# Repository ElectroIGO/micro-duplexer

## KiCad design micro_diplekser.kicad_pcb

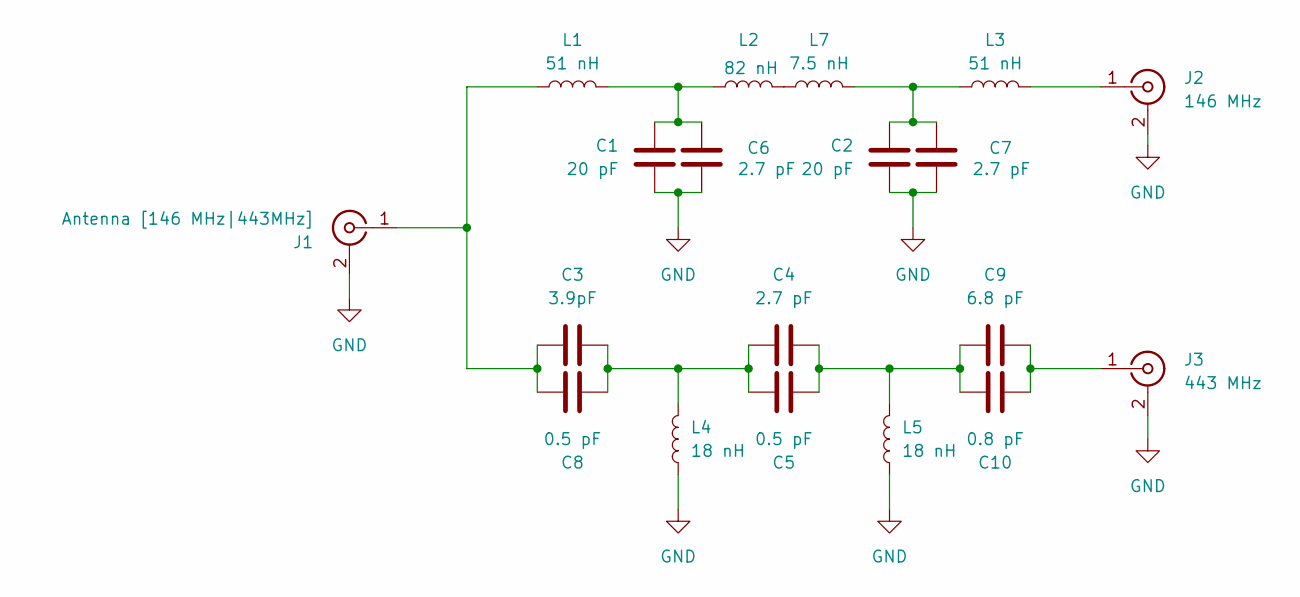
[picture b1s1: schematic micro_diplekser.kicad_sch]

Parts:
C1, C2: 20 pF; C_0603_1608Metric
C3: 3.9pF; C_0603_1608Metric
C4, C6, C7: 2.7 pF; C_0603_1608Metric
C5, C8: 0.5 pF; C_0603_1608Metric
C9: 6.8 pF; C_0603_1608Metric
C10: 0.8 pF; C_0603_1608Metric
J1: Antenna [146 MHz|443MHz]; SMA_CHINA
J2: 146 MHz; SMA_CHINA
J3: 443 MHz; SMA_CHINA
L1, L3: 51 nH; L_0603_1608Metric
L2: 82 nH; L_0603_1608Metric
L4, L5: 18 nH; L_0603_1608Metric
L7: 7.5 nH; L_0603_1608Metric

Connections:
GND: C1.2, C2.2, C6.2, C7.2, J1.2 (Ext), J2.2 (Ext), J3.2 (Ext), L4.1, L5.1
unnamed: C1.1, C6.1, L1.2, L2.1
unnamed: C2.1, C7.1, L3.1, L7.2
unnamed: C3.2, C4.1, C5.1, C8.2, L4.2
unnamed: C4.2, C5.2, C9.1, C10.1, L5.2
unnamed: C3.1, C8.1, J1.1 (In), L1.1
unnamed: J2.1 (In), L3.2
unnamed: C9.2, C10.2, J3.1 (In)
unnamed: L2.2, L7.1

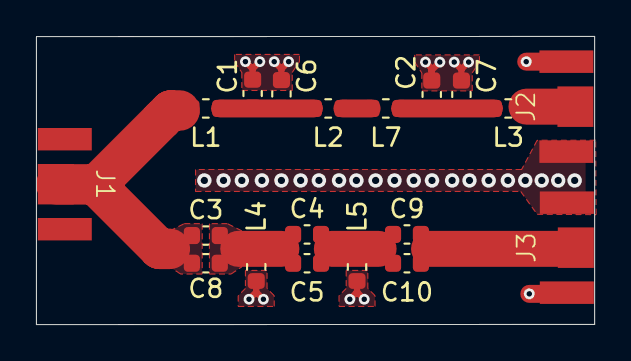
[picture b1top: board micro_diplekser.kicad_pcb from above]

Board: 2 copper layers, 31.0 x 16.0 mm, 19 parts (0 on the bottom side), 9 nets.

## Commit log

2024-09-10 Last modifications
2024-09-10 Improved version - better S1.1 S2.2 and S3.3 parameters, bigger width and dBm, but decrease isolation between port 3 and port 2 by 5 dBm. Made whole design with 0603 components, not mixing size like 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
2024-09-10 renamed gitignore file
